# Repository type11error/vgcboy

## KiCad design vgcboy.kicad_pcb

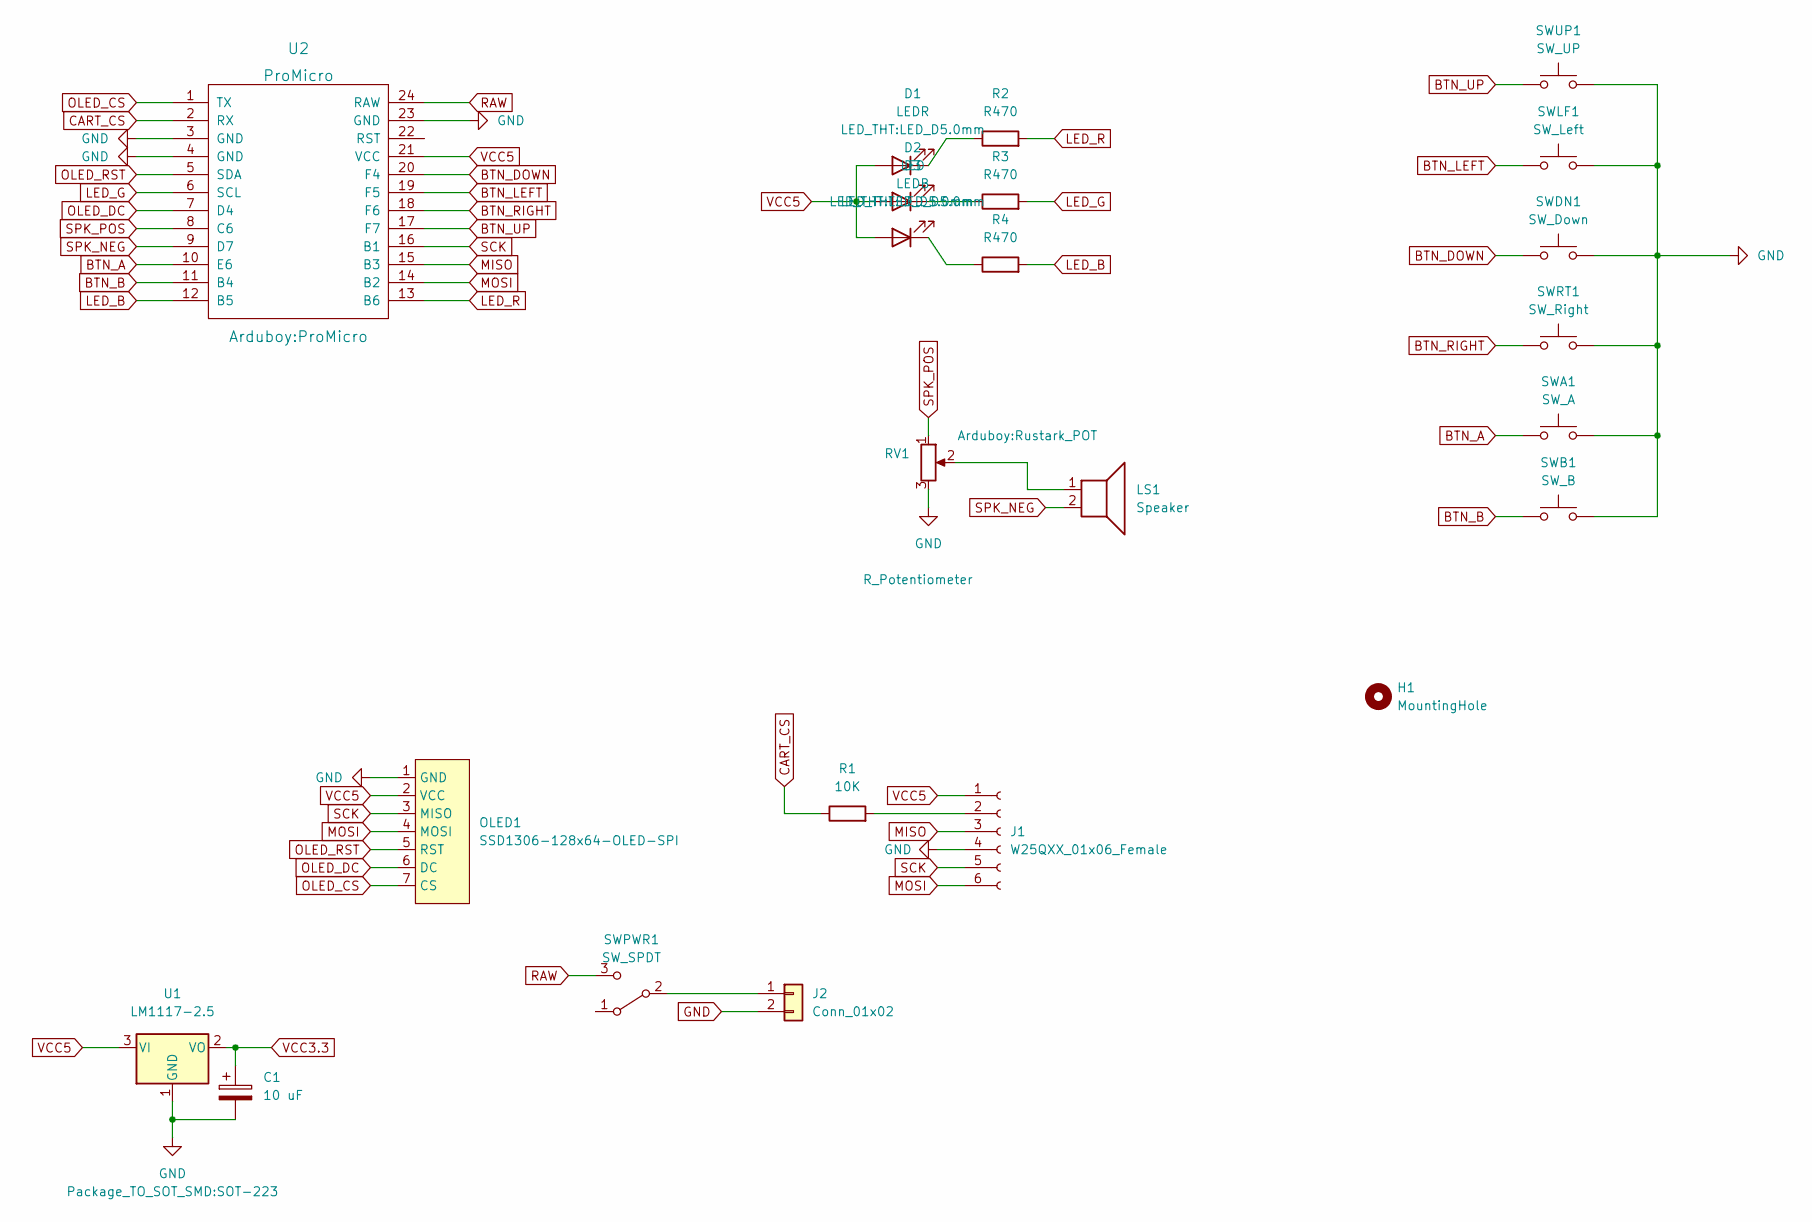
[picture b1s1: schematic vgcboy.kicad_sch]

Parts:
C1: 10 uF; C_1206_3216Metric_Pad1.33x1.80mm_HandSolder
D1: LEDR; LED_D5.0mm
D2: LED; LED_D5.0mm
D3: LEDB; LED_D5.0mm
H1: MountingHole; MountingHole_8.4mm_M8
J1: W25QXX_01x06_Female; PinHeader_1x06_P2.54mm_Vertical
J2: Conn_01x02; PinHeader_1x02_P2.54mm_Vertical
LS1: Speaker; Pizo
OLED1: SSD1306-128x64-OLED-SPI
R1: 10K; R_Axial_DIN0309_L9.0mm_D3.2mm_P12.70mm_Horizontal
R2, R3, R4: R470; R_Axial_DIN0309_L9.0mm_D3.2mm_P12.70mm_Horizontal
RV1: R_Potentiometer; Rustark_POT
SWA1: SW_A; SW_PUSH_6mm_H5mm
SWB1: SW_B; SW_PUSH_6mm_H5mm
SWDN1: SW_Down; SW_PUSH_6mm_H5mm
SWLF1: SW_Left; SW_PUSH_6mm_H5mm
SWPWR1: SW_SPDT; SS-12F23 Switch
SWRT1: SW_Right; SW_PUSH_6mm_H5mm
SWUP1: SW_UP; SW_PUSH_6mm_H5mm
U1: LM1117-2.5; SOT-223
U2: ProMicro

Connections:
BTN_A: SWA1.1, U2.10 (E6)
BTN_B: SWB1.1, U2.11 (B4)
BTN_DOWN: SWDN1.1, U2.20 (F4)
BTN_LEFT: SWLF1.1, U2.19 (F5)
BTN_RIGHT: SWRT1.1, U2.18 (F6)
BTN_UP: SWUP1.1, U2.17 (F7)
CART_CS: R1.1, U2.2 (RX)
GND: C1.2, J1.4, J2.2, OLED1.1 (GND), RV1.3, SWA1.2, SWB1.2, SWDN1.2, SWLF1.2, SWRT1.2, SWUP1.2, U1.1 (GND), U2.3 (GND), U2.4 (GND), U2.23 (GND)
LED_B: R4.2, U2.12 (B5)
LED_G: R3.2, U2.6 (SCL)
LED_R: R2.2, U2.13 (B6)
MISO: J1.3, U2.15 (B3)
MOSI: J1.6, OLED1.4 (MOSI), U2.14 (B2)
unnamed: D1.1 (K), R2.1
unnamed: D2.1 (K), R3.1
unnamed: D3.1 (K), R4.1
unnamed: J1.2, R1.2
unnamed: J2.1, SWPWR1.2 (B)
unnamed: LS1.1, RV1.2
OLED_CS: OLED1.7 (CS), U2.1 (TX)
OLED_DC: OLED1.6 (DC), U2.7 (D4)
OLED_RST: OLED1.5 (RST), U2.5 (SDA)
RAW: SWPWR1.3 (C), U2.24 (RAW)
SCK: J1.5, OLED1.3 (MISO), U2.16 (B1)
SPK_NEG: LS1.2, U2.9 (D7)
SPK_POS: RV1.1, U2.8 (C6)
VCC3.3: C1.1, U1.2 (VO)
VCC5: D1.2 (A), D2.2 (A), D3.2 (A), J1.1, OLED1.2 (VCC), U1.3 (VI), U2.21 (VCC)

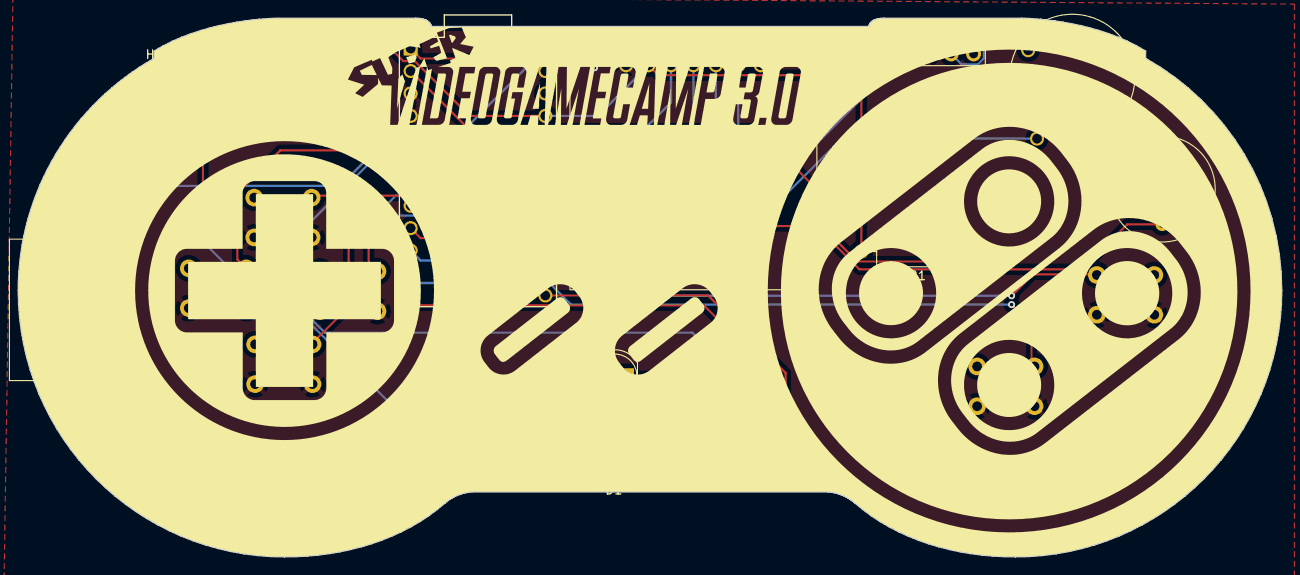
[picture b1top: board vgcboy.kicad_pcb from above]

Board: 2 copper layers, 143.0 x 61.0 mm, 23 parts (0 on the bottom side), 28 nets.
